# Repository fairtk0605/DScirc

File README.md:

# DScirc
Simple DC Voltage Generater with ON-OFF Signal using Arduino

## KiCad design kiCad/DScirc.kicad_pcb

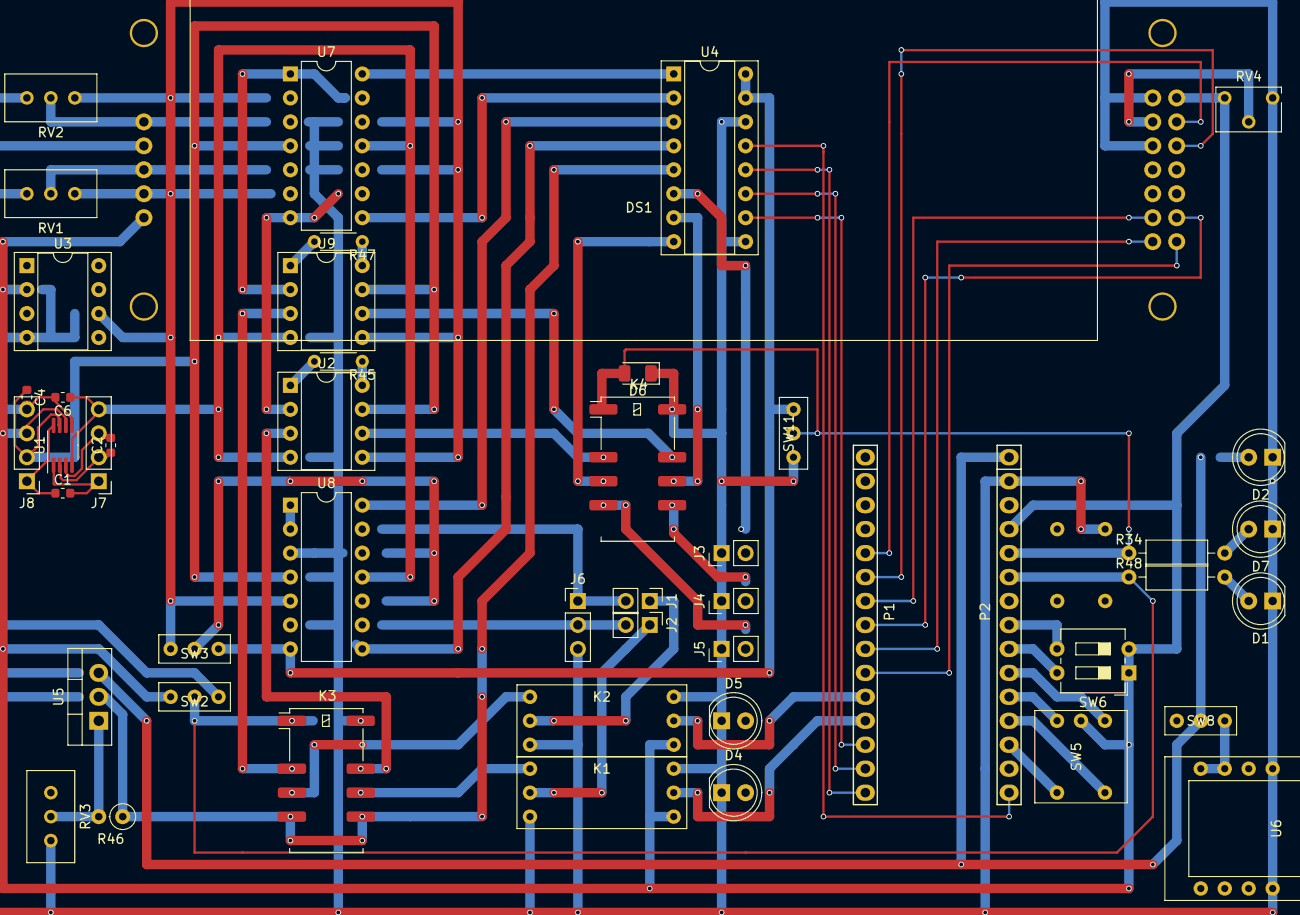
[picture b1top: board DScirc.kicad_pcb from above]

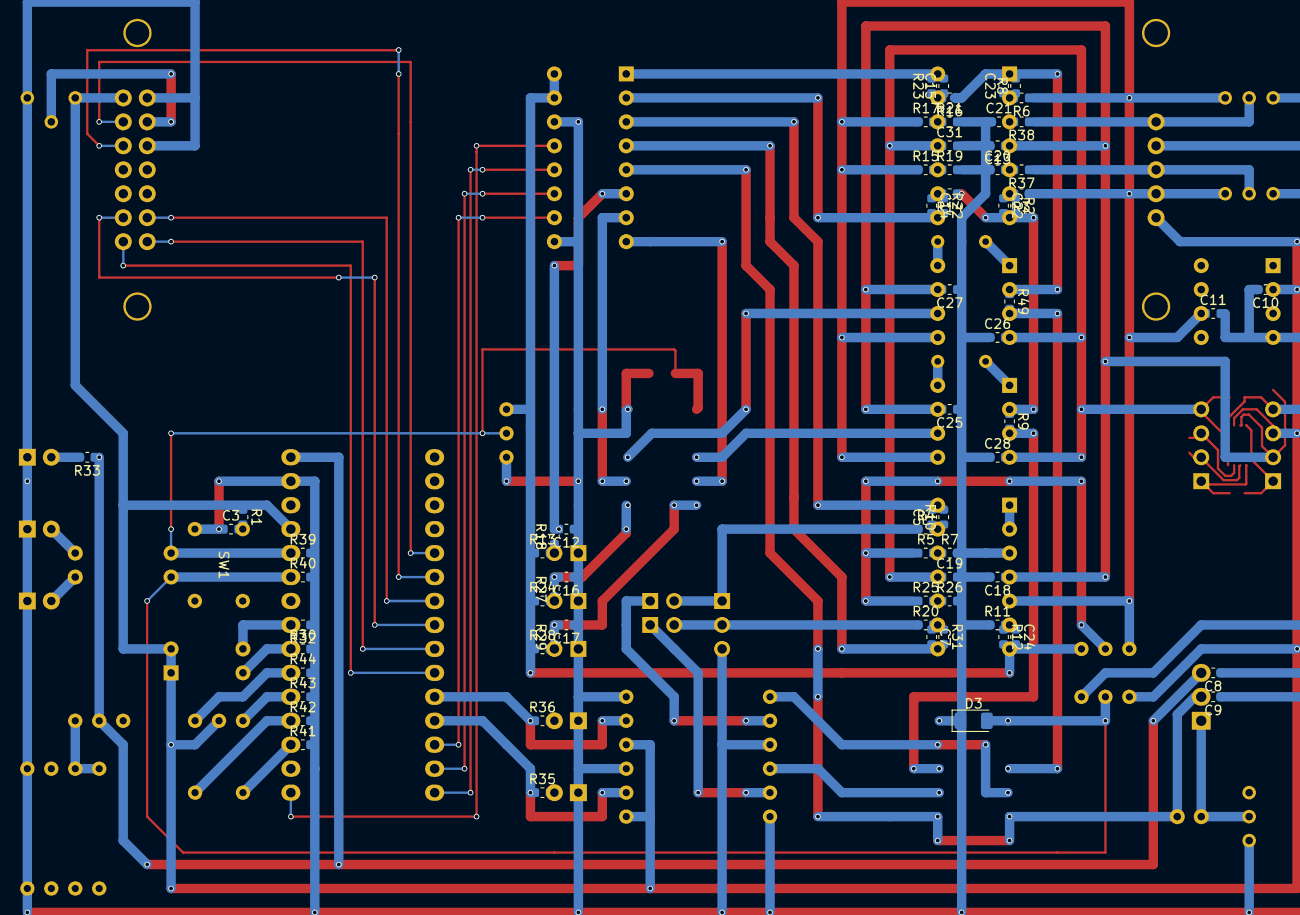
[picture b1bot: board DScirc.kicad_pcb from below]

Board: 2 copper layers, 120 parts (71 on the bottom side), 87 nets.

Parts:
C1, C2, C3, C4, C5, C6, C7, C8, C9, C11, C12, C13, C14, C15, C16, C17, C18, C19, C20, C21, C22, C23, C24, C25, C26, C27, C28, C31: 100n; C_0603_1608Metric
C10: 1u; C_0603_1608Metric
D1, D2, D4, D5, D7: LED; LED_D5.0mm
D3, D6: DIODE; D_1206_3216Metric
DS1: sc2004
J1, J2, J3, J4, J5: Conn_01x02; PinHeader_1x02_P2.54mm_Vertical
J6: Conn_01x03; PinHeader_1x03_P2.54mm_Vertical
J7, J8: Conn_01x04; PinHeader_1x04_P2.54mm_Vertical
K1, K2: Simple_SPDT_Relay
K3, K4: EE2-5NU; Relay_DPDT_Kemet_EE2_NU
P1: Digital; Socket_Strip_Arduino_1x15
P2: Analog; Socket_Strip_Arduino_1x15
R1, R4, R5, R7, R10, R11, R12, R14, R15, R16, R17, R19, R20, R21, R22, R23, R25, R26, R30, R31, R32, R33, R35, R36, R39, R40, R41, R42, R43, R44: 10k; R_0603_1608Metric
R2, R3, R6, R8, R13, R18, R24, R27, R28, R29, R37, R38: 20k; R_0603_1608Metric
R9, R49: 10; R_0603_1608Metric
R34, R48: 10k; R_Axial_DIN0207_L6.3mm_D2.5mm_P10.16mm_Horizontal
R45, R47: 100; R_Axial_DIN0204_L3.6mm_D1.6mm_P5.08mm_Horizontal
R46: 150; R_Axial_DIN0207_L6.3mm_D2.5mm_P2.54mm_Vertical
RV1, RV2, RV3: R_POT_10k; Potentiometer_Bourns_3296W_Vertical
RV4: R_POT_500; Potentiometer_Bourns_3266W_Vertical
SW1: OnOff; SW_Push
SW2, SW3, SW8, SW11: SW_SPDT
SW5: SW_Coded_SH-7050; Rotery_DIP_16
SW6: SW_DIP_x02; SW_DIP_SPSTx02_Slide_6.7x6.64mm_W7.62mm_P2.54mm_LowProfile
U1: Max865; MSOP-8_3x3mm_P0.65mm
U2, U9: AD620; DIP-8_W7.62mm_Socket
U3: AD780; DIP-8_W7.62mm_Socket
U4: MCP3208; DIP-16_W7.62mm_Socket
U5: LM317_TO-220; TO-220-3_Vertical
U6: DC_Juck; DC_Jack
U7, U8: TL084; DIP-14_W7.62mm

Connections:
+5V: C10.1, DS1.2, DS1.15, J8.3, K1.1, K2.1, P2.4, R1.1, RV4.3, SW2.1, SW5.C, SW6.1, SW6.2, U1.6, U3.2
+10V: C4.1, C13.1, C18.1, C25.2, C27.2, J8.2, U1.7, U2.7, U7.4, U8.4, U9.7
+12VA: C8.2, P2.1, R33.1, SW8.2, U5.3
-10V: C6.1, C19.1, C26.2, C28.2, C31.1, J7.4, U1.4, U2.4, U7.11, U8.11, U9.4
/2: DS1.4, P1.5
/2.5VA: C11.1, DS1.15, R3.1, R6.1, R15.1, R17.1, RV1.3, RV2.3, SW3.1, U2.5, U3.6, U8.5, U9.5
/3(**): DS1.6, P1.6
/4: DS1.11, P1.7
/5(**): DS1.12, P1.8
/5VA: C24.2, R12.2, R13.1, R24.1, R28.1, SW3.3, SW11.1, U4.15, U4.16, U8.7
/6(**): DS1.13, P1.9
/7: DS1.14, P1.10
/8: K2.2, P1.11, R36.1
/9(**): K1.2, P1.12, R35.1
/10(**/SS): P1.13, U4.10
/11(**/MOSI): P1.14, U4.11
/12(MISO): P1.15, U4.12
/13(SCK): P2.15, U4.13
/A0: P2.12, R42.1, SW5.2
/A1: P2.11, R43.1, SW5.4
/A2: P2.10, R44.1, SW5.8
/A3: P2.9, R30.1, SW6.4
/A4: P2.8, R32.2, SW6.3
/A5: C3.2, P2.7, R1.2, SW1.2
/A6: D3.2, K3.1, P2.6, R40.1, R48.1, SW2.2
/A7: D6.2, K4.1, P2.5, R34.1, R39.1, SW11.2
/AREF: P2.13, R41.1, SW5.1
/CH1: J2.2, J6.2, R20.1
/CH1_ADC: C14.2, R22.2, U4.2, U7.8
/CH1_ADC_M: C7.2, R31.2, U4.4, U8.8
/CH1_Current: K4.3, U2.6
/CH1_N: K3.10, R9.2, U2.3
/CH1_Out: C22.2, R2.2, R9.1, R14.1, U2.2, U7.7
/CH2: J1.2, J6.1, R4.1
/CH2_ADC: C15.2, R23.2, U4.1, U7.14
/CH2_ADC_M: C5.2, R10.2, U4.3, U8.14
/CH2_Current: K4.10, U9.6
/CH2_N: K3.3, R49.2, U9.3
/CH2_Out: C23.2, R8.2, R16.1, R49.1, U7.1, U9.2
/CH3_Out: C9.2, K3.5, K3.8, R46.1, U4.5, U5.2
/Measure02: K4.9, U4.7
/Measure03: K4.4, U4.8
/Ref: R5.1, R25.1, SW3.2
/Reset: P1.3, P2.3
/Temp01: C12.2, R18.2, U4.6
/Temp02: C16.2, K4.8, R27.2
/Temp03: C17.2, K4.5, R29.2
/Vin: SW8.3, U6.1, U6.2, U6.7, U6.8
GND: C3.1, C4.2, C6.2, C8.1, C9.1, C10.2, C11.2, C12.1, C13.2, C16.1, C17.1, C18.2, C19.2, C20.1, C21.1, C25.1, C26.1, C27.1, C28.1, C31.2, D1.1, D2.1, D3.1, D4.1, D5.1, D6.1, D7.1, DS1.1, DS1.5, DS1.16, J3.1, J4.1, J5.1, J6.3, J8.4, K1.3, K1.4, K2.3, K2.4, K3.12, K4.12, P1.4, P2.2, R7.2, R11.1, R19.2, R21.2, R26.2, R30.2, R32.1, R39.2, R40.2, R41.2, R42.2, R43.2, R44.2, RV1.1, RV2.1, RV3.1, RV4.1, SW1.1, SW2.3, SW11.3, U1.5, U3.4, U4.9, U4.14, U6.3, U6.4, U6.5, U6.6, U8.3
unnamed: C1.1, J8.1, U1.8
unnamed: C1.2, J7.1, U1.1
unnamed: C2.1, J7.2, U1.2
unnamed: C2.2, J7.3, U1.3
unnamed: C5.1, R4.2, R10.1, U8.13
unnamed: C7.1, R20.2, R31.1, U8.9
unnamed: C14.1, R14.2, R22.1, U7.9
unnamed: C15.1, R16.2, R23.1, U7.13
unnamed: C20.2, R37.2, U7.5
unnamed: C21.2, R38.2, U7.3
unnamed: C22.1, R2.1, R3.2, U7.6
unnamed: C23.1, R6.2, R8.1, U7.2
unnamed: C24.1, R11.2, R12.1, U8.6
unnamed: D1.2, R48.2
unnamed: D2.2, R33.2
unnamed: D4.2, R35.2
unnamed: D5.2, R36.2
unnamed: D7.2, R34.2
unnamed: DS1.3, RV4.2
unnamed: J1.1, K2.5
unnamed: J2.1, K1.5
unnamed: J3.2, R13.2, R18.1
unnamed: J4.2, R24.2, R27.1
unnamed: J5.2, R28.2, R29.1
unnamed: K1.6, K3.9
unnamed: K2.6, K3.4
unnamed: R5.2, R7.1, U8.12
unnamed: R15.2, R19.1, U7.10
unnamed: R17.2, R21.1, U7.12
unnamed: R25.2, R26.1, U8.10
unnamed: R37.1, RV1.2
unnamed: DS1.16, R38.1, RV2.2
unnamed: R45.1, U2.8
unnamed: R45.2, U2.1
unnamed: R46.2, RV3.2, U5.1
unnamed: R47.1, U9.8
unnamed: R47.2, U9.1
unnamed: U8.1, U8.2

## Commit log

2023-04-07 ユニバーサル基盤用に作製した回路図・レイアウトのファイルを追加。ライブラリも追加。
2023-04-09 Action追加
    GitHub Actions用のファイルを追加した。回路図と基板データをPDFにするとされているアクション。
2023-04-09 Revert "ユニバーサル基盤用に作製した回路図・レイアウトのファイルを追加。ライブラリも追加。"
    This reverts commit bfbea26ff8d5e86dd08cb8e3791c971e786978e6.
